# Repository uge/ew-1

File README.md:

# Pi 5 Corona HV supply

The canonical working design is **N-layout-17-hv-warnings**. Open
[pi5_corona_hv.kicad_pro](hardware/pi5_corona_hat_direct/pi5_corona_hv.kicad_pro)
in **KiCad 10**. This is the active editable project, including the accepted
component substitutions, completed routing and front/back high-voltage warnings.

- [Project guide](hardware/pi5_corona_hat_direct/README.md)
- [Current JLCPCB package](hardware/pi5_corona_hat_direct/exports/jlcpcb-N-layout-17-hv-warnings-package.zip)
- [Front preview](hardware/pi5_corona_hat_direct/renders/hv-warning-front.png) / [back preview](hardware/pi5_corona_hat_direct/renders/hv-warning-back.png)
- [Design status and unresolved issues](hardware/pi5_corona_hat_direct/AUDIT.md)
- [Export and validation commands](hardware/pi5_corona_hat_direct/layout/README.md)

Old project copies, trial boards, revision snapshots and stale generated outputs
have been removed from the working tree. Earlier tracked versions remain in Git
history. Historical design notes under `docs/` are reference material; the project
guide and native files above take precedence. The `doc` link is an alias of `docs`.

The working version is not a qualified 15 kV production release. Native ERC/DRC
checks do not replace the outstanding insulation, surge and component qualification.

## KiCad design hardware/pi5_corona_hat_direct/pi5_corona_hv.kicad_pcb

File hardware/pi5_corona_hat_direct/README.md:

# Working design — N-layout-17-hv-warnings

Open `pi5_corona_hv.kicad_pro` in KiCad 10. The adjacent PCB, root schematic,
five hierarchical sheets, custom symbol/footprint libraries and 3D assets form
the single working project. Standard KiCad 10 libraries must be installed separately.
Keep all these project files together; library tables use `${KIPRJMOD}` paths.

The board is two-layer, 1.6 mm thick, with a 196 × 120 mm carrier and five
break-off mini boards (231 × 120 mm overall envelope). Accepted LV routing,
the shortened HV return surge path and large warning graphics on both sides
are present in the native PCB. DNP parts are C63/R64; MP1 is a DNP mechanical reference.

| References | Current selection |
|---|---|
| C100–C111 | STE A12B1D102KN0B0S0N0 / C249245; 1 nF, 6 kV, Y5P, 10%, 10 mm pitch |
| R20–R29 | Bourns CHV2512-JW-106ELF / C2095568; 10 MΩ, 5%, 1 W, 3 kV, 2512 |
| D51 | hongjiacheng SMBJ22A / C49066946 |
| T1 | Coilcraft FL2015-4LD; external sourcing required |

Use the current JLCPCB deliverables for Gerbers/drills, BOM and CPL: 159 components
across 53 matching BOM rows. `exports/jlcpcb-bom.csv`, `exports/jlcpcb-cpl.csv` and
`exports/jlcpcb-gerbers.zip` are the upload files. Only T1 remains a purchased-component
external-source exception. DNP parts and PCB-only features are excluded.

[Front](renders/hv-warning-front.png) and [back](renders/hv-warning-back.png)
previews show current markings. These are diagnostic layer previews, not 3D assembly
fit certification. Dated procurement evidence remains under `procurement/`.
Stock evidence is a snapshot, not a reservation or guarantee of orderability.

[Pi 5 host runbook](host/RUNBOOK.md) prepares ew-1 for the board; [Pi Zero 2W mixed AP guide](host/ZERO2W_MIXED_AP.md) configures `ew-1-zero-2w.local` for concurrent Wi-Fi client + AP operation; [bring-up log](host/BRINGUP.md), [handoff summary](host/HANDOFF.md), and [HUSB238A notes](host/HUSB238A.md) record current bench state and USB-PD driver behavior.
[Validation/export instructions](layout/README.md) reproduce current outputs.
[Design status](AUDIT.md) records the unresolved HV and procurement issues.
The native files are the working design, not an archival or experimental copy.
Earlier tracked versions can be recovered from Git history.

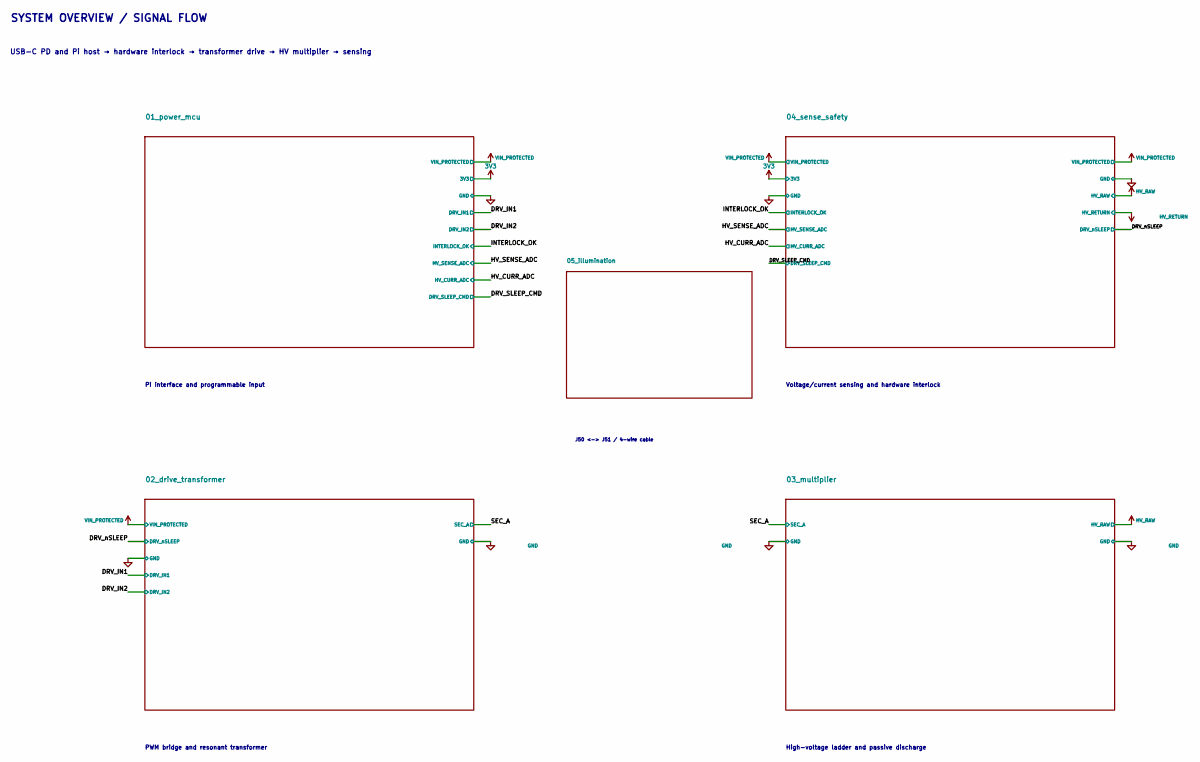
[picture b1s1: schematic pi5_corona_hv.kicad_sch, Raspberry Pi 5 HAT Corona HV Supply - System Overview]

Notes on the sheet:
SYSTEM OVERVIEW / SIGNAL FLOW
High-voltage ladder and passive discharge
Pi interface and programmable input
J50 <-> J51 / 4-wire cable
Voltage/current sensing and hardware interlock
USB-C PD and Pi host → hardware interlock → transformer drive → HV multiplier → sensing
PWM bridge and resonant transformer

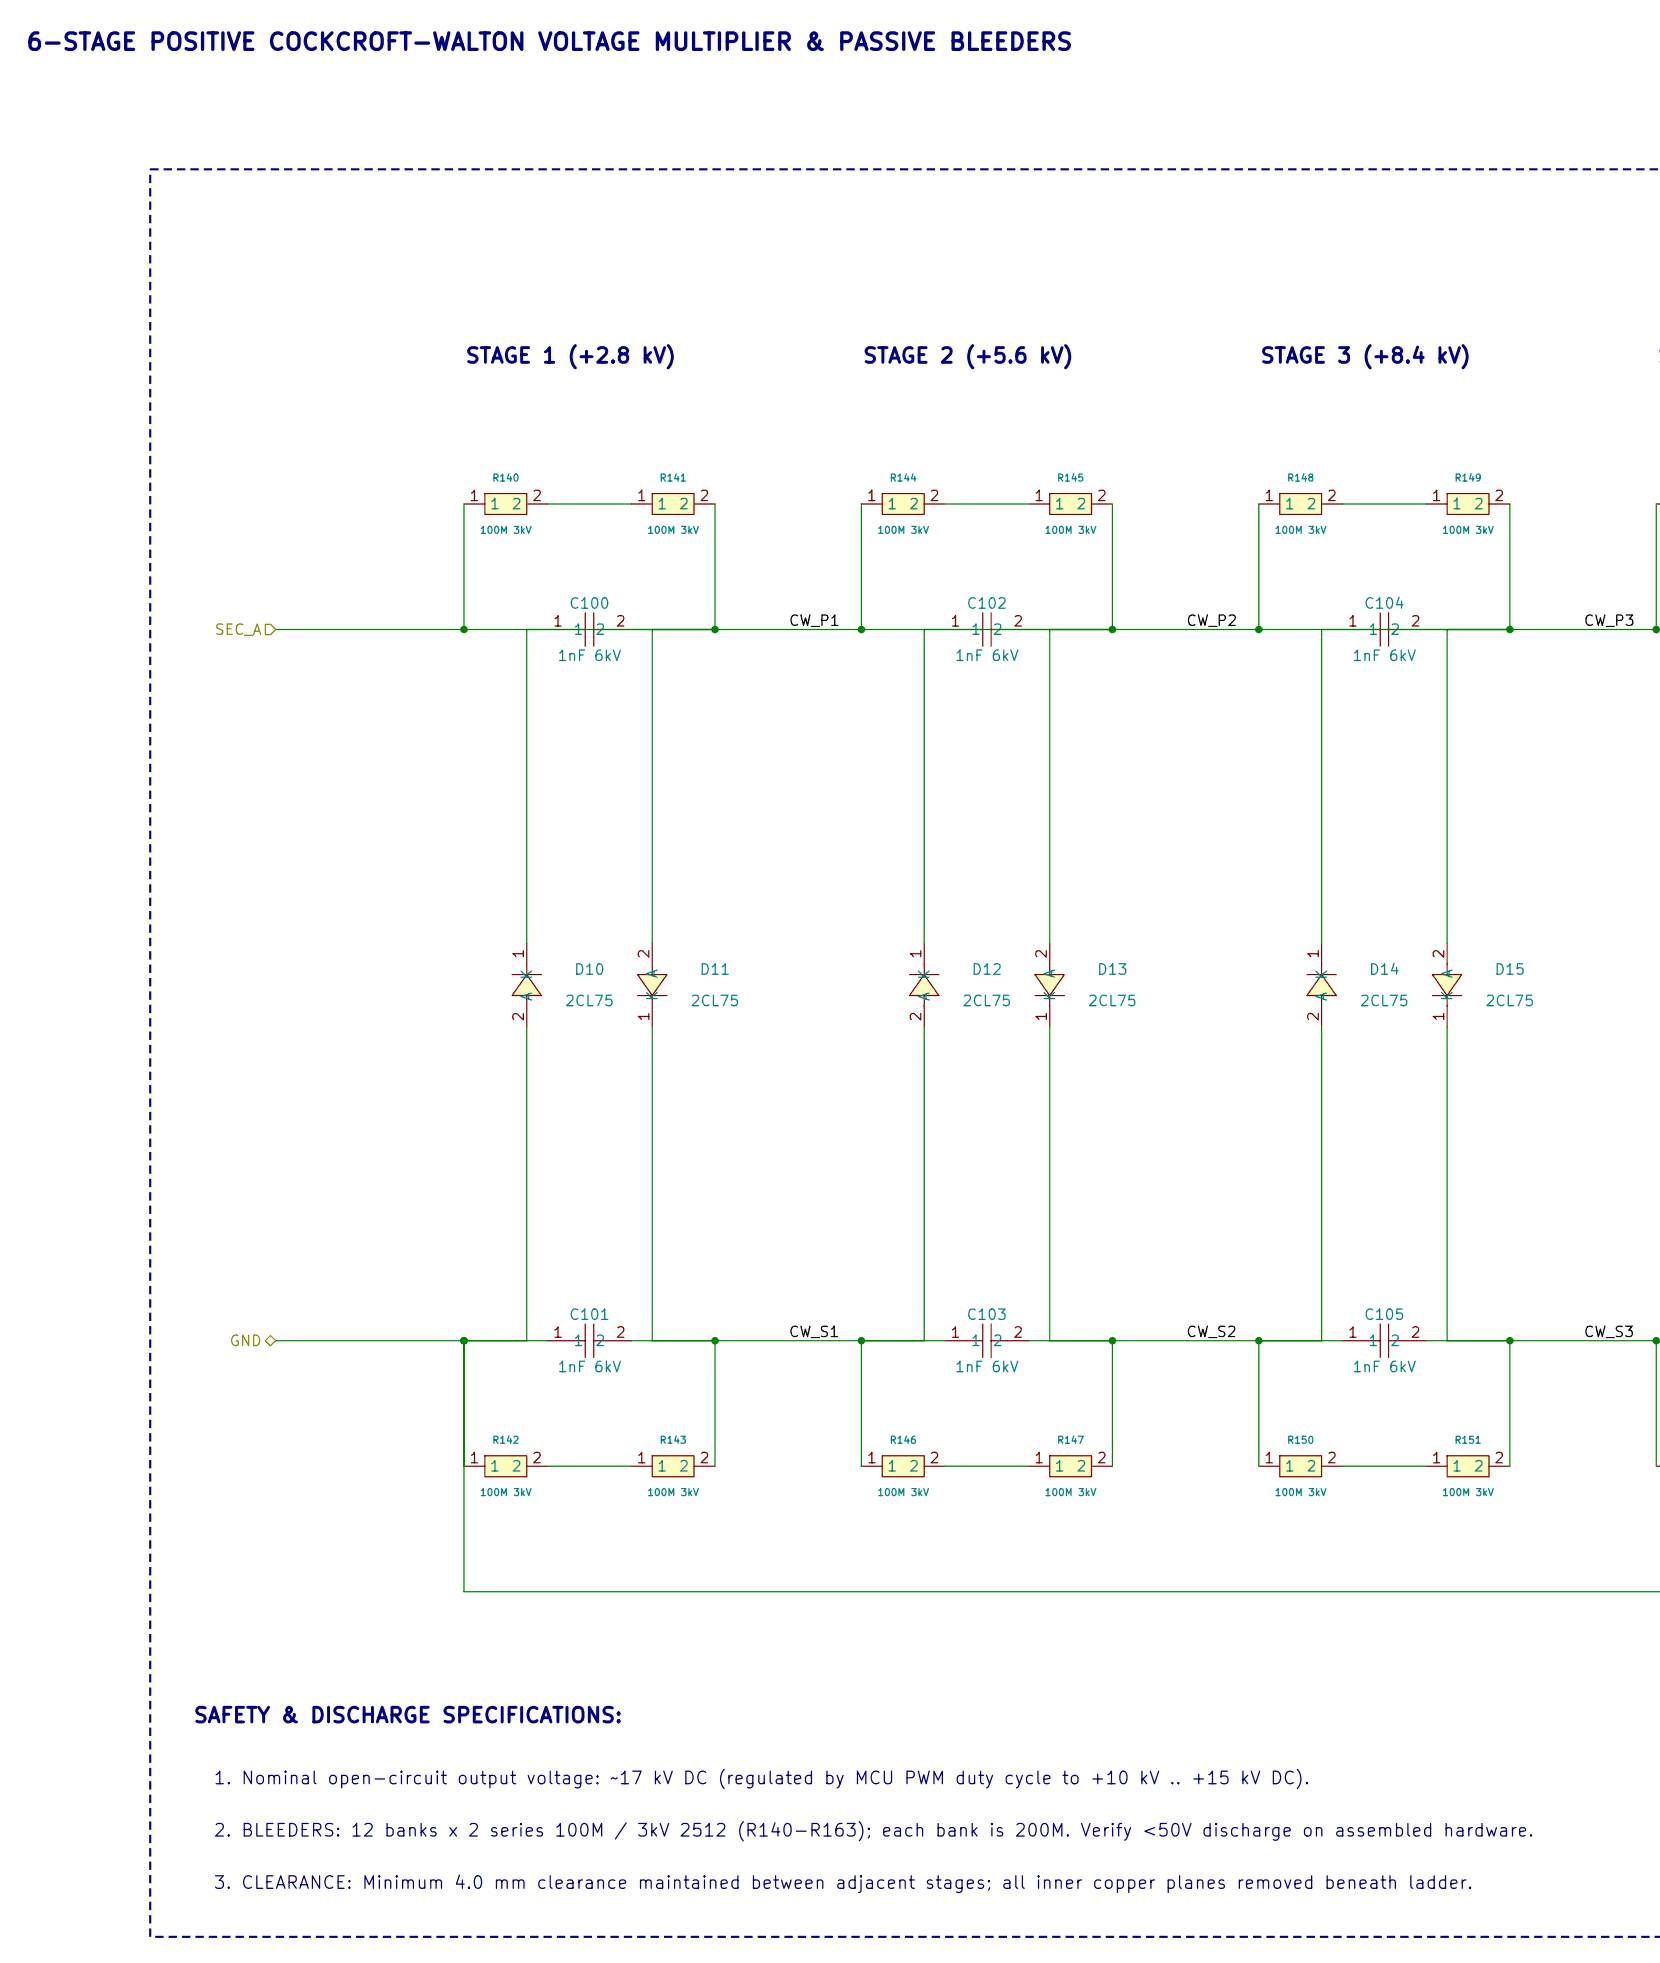
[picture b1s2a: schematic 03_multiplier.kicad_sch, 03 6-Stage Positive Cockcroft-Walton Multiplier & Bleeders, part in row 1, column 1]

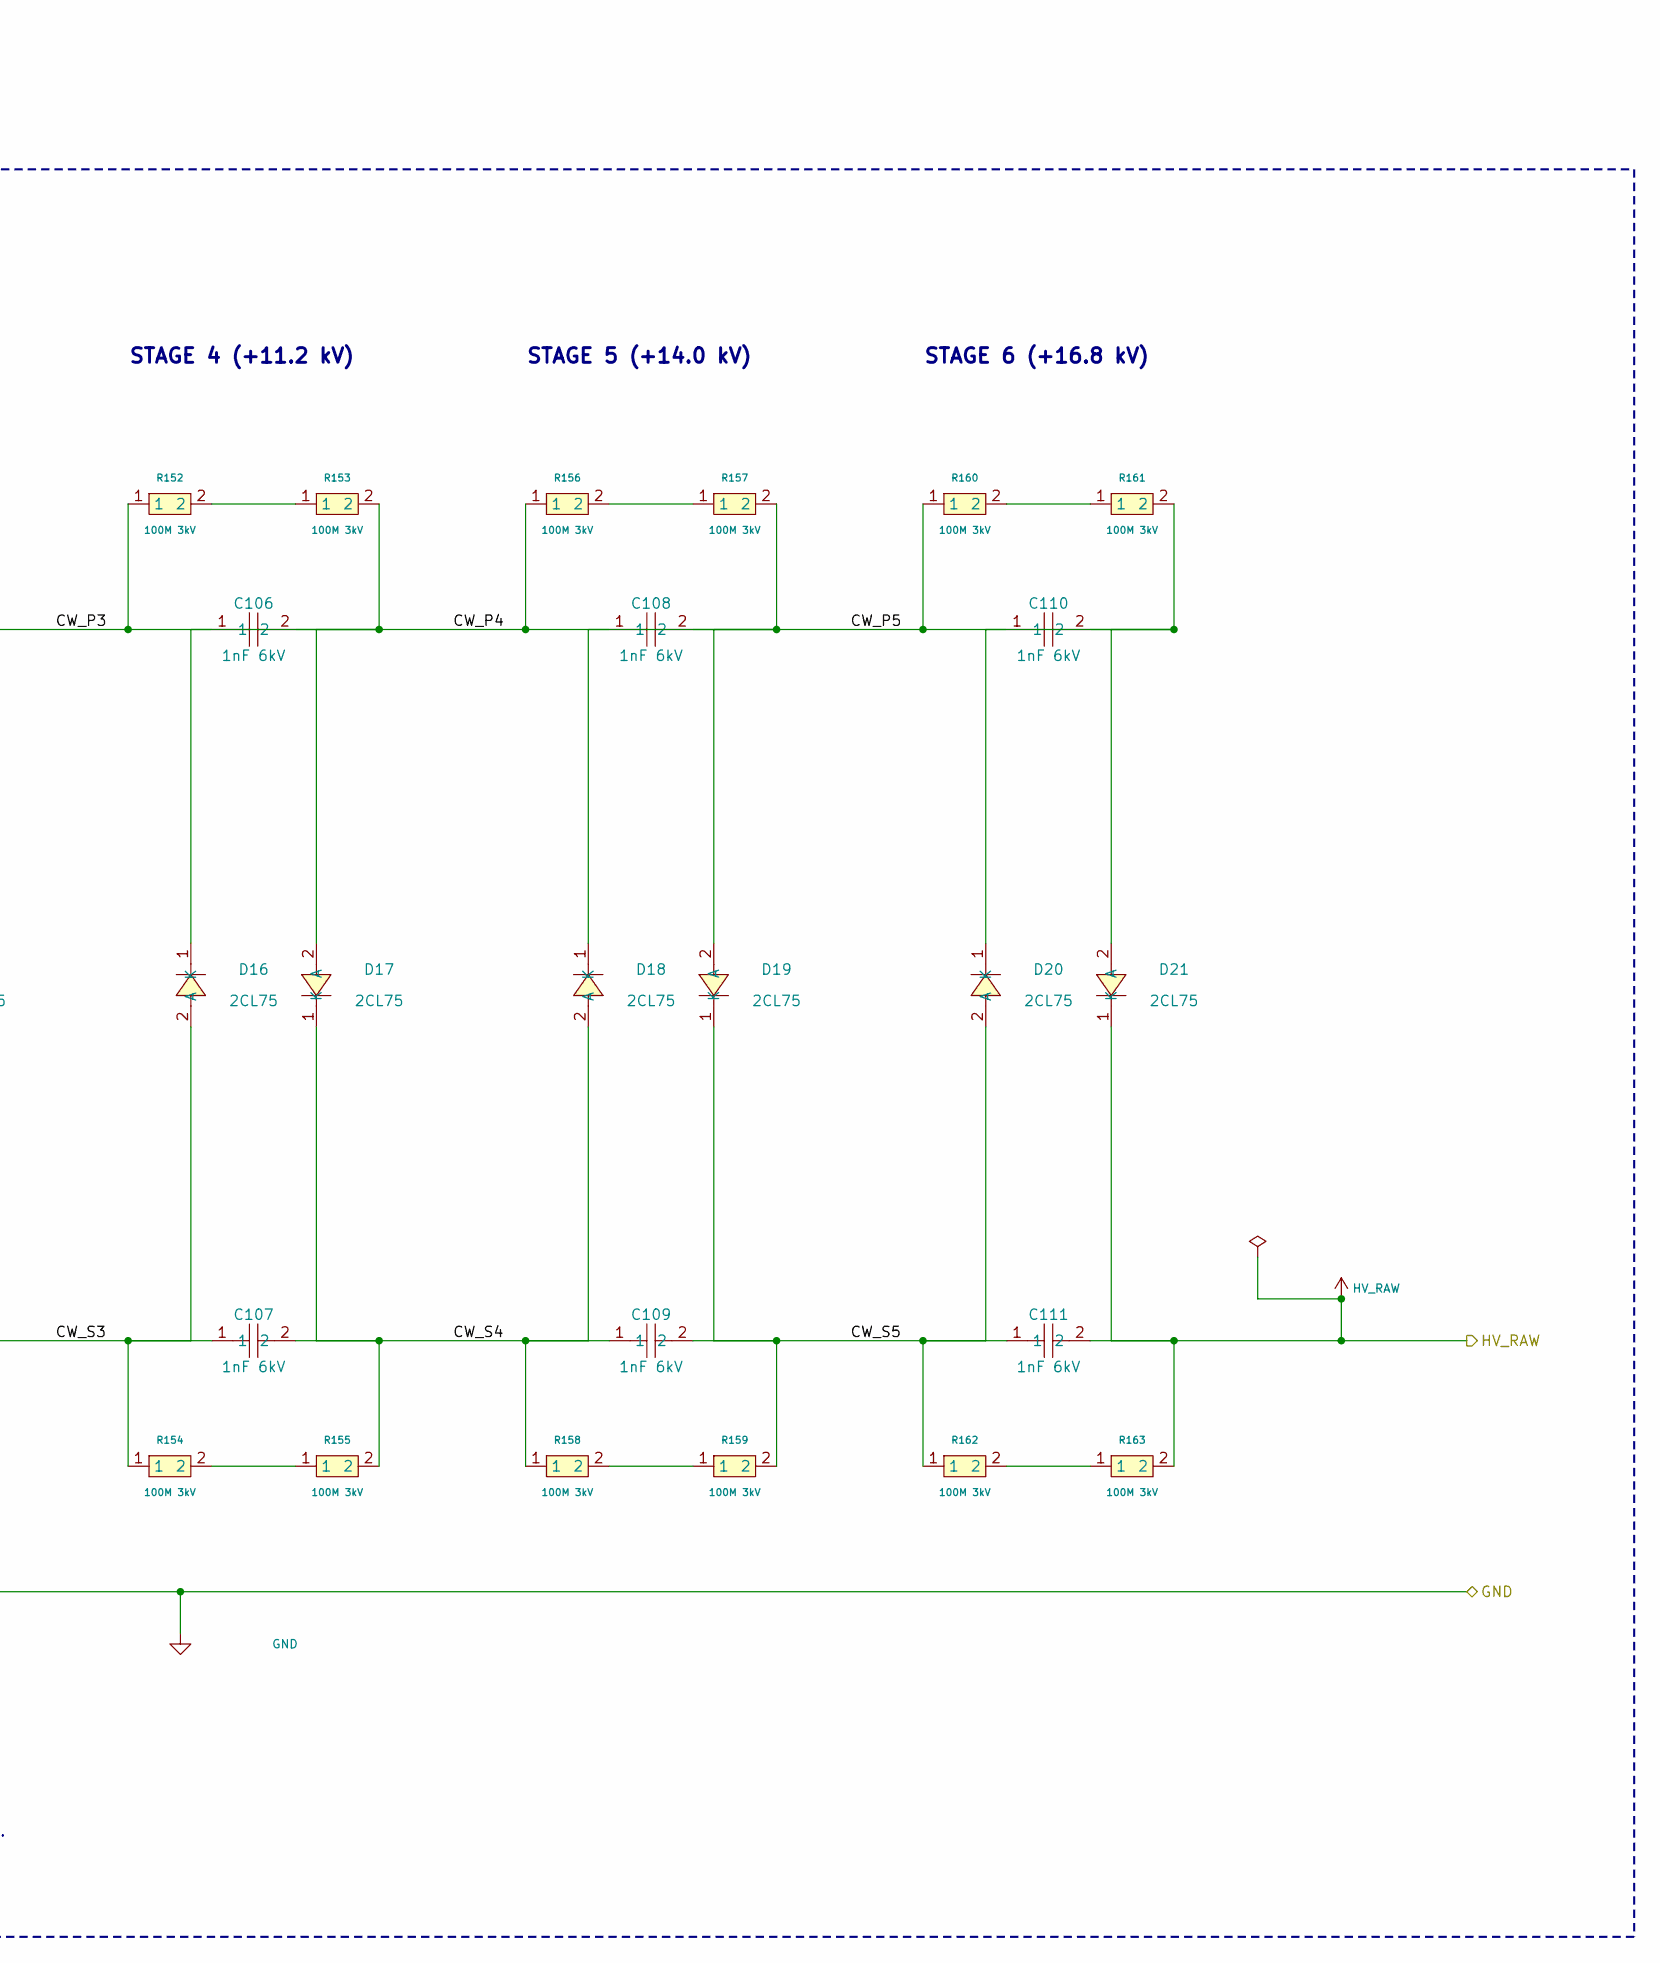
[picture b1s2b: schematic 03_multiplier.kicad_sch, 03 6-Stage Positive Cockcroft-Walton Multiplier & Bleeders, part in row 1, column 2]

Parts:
C100, C101, C102, C103, C104, C105, C106, C107, C108, C109, C110, C111: 1nF 6kV; STE_A12B1D102K_P10.0mm; MPN A12B1D102KN0B0S0N0; LCSC Part C249245
D10, D11, D12, D13, D14, D15, D16, D17, D18, D19, D20, D21: 2CL75; Sunmate_2CL75_D3_L12_P26; MPN 2CL75; LCSC Part C424512
R140, R141, R142, R143, R144, R145, R146, R147, R148, R149, R150, R151, R152, R153, R154, R155, R156, R157, R158, R159, R160, R161, R162, R163: 100M 3kV; R_2512_6332Metric; MPN CHV2512-JW-107ELF; LCSC Part C2089706

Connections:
/03_multiplier/CW_P1: C100.2, C102.1, D10.1 (K), D11.2 (A), R141.2, R144.1
/03_multiplier/CW_P2: C102.2, C104.1, D12.1 (K), D13.2 (A), R145.2, R148.1
/03_multiplier/CW_P3: C104.2, C106.1, D14.1 (K), D15.2 (A), R149.2, R152.1
/03_multiplier/CW_P4: C106.2, C108.1, D16.1 (K), D17.2 (A), R153.2, R156.1
/03_multiplier/CW_P5: C108.2, C110.1, D18.1 (K), D19.2 (A), R157.2, R160.1
/03_multiplier/CW_S1: C101.2, C103.1, D11.1 (K), D12.2 (A), R143.2, R146.1
/03_multiplier/CW_S2: C103.2, C105.1, D13.1 (K), D14.2 (A), R147.2, R150.1
/03_multiplier/CW_S3: C105.2, C107.1, D15.1 (K), D16.2 (A), R151.2, R154.1
/03_multiplier/CW_S4: C107.2, C109.1, D17.1 (K), D18.2 (A), R155.2, R158.1
/03_multiplier/CW_S5: C109.2, C111.1, D19.1 (K), D20.2 (A), R159.2, R162.1
/HV_RAW: C111.2, D21.1 (K), R163.2; also elsewhere on the board
/SEC_A: C100.1, R140.1; also elsewhere on the board
GND: C101.1, D10.2 (A), R142.1; also elsewhere on the board
unnamed: C110.2, D20.1 (K), D21.2 (A), R161.2
unnamed: R140.2, R141.1
unnamed: R142.2, R143.1
unnamed: R144.2, R145.1
unnamed: R146.2, R147.1
unnamed: R148.2, R149.1
unnamed: R150.2, R151.1
unnamed: R152.2, R153.1
unnamed: R154.2, R155.1
unnamed: R156.2, R157.1
unnamed: R158.2, R159.1
unnamed: R160.2, R161.1
unnamed: R162.2, R163.1

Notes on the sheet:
SAFETY & DISCHARGE SPECIFICATIONS:
STAGE 2 (+5.6 kV)
STAGE 3 (+8.4 kV)
STAGE 4 (+11.2 kV)
STAGE 6 (+16.8 kV)
2. BLEEDERS: 12 banks x 2 series 100M / 3kV 2512 (R140-R163); each bank is 200M. Verify <50V discharge on assembled hardware.
STAGE 1 (+2.8 kV)
3. CLEARANCE: Minimum 4.0 mm clearance maintained between adjacent stages; all inner copper planes removed beneath ladder.
6-STAGE POSITIVE COCKCROFT-WALTON VOLTAGE MULTIPLIER & PASSIVE BLEEDERS
1. Nominal open-circuit output voltage: ~17 kV DC (regulated by MCU PWM duty cycle to +10 kV .. +15 kV DC).
STAGE 5 (+14.0 kV)

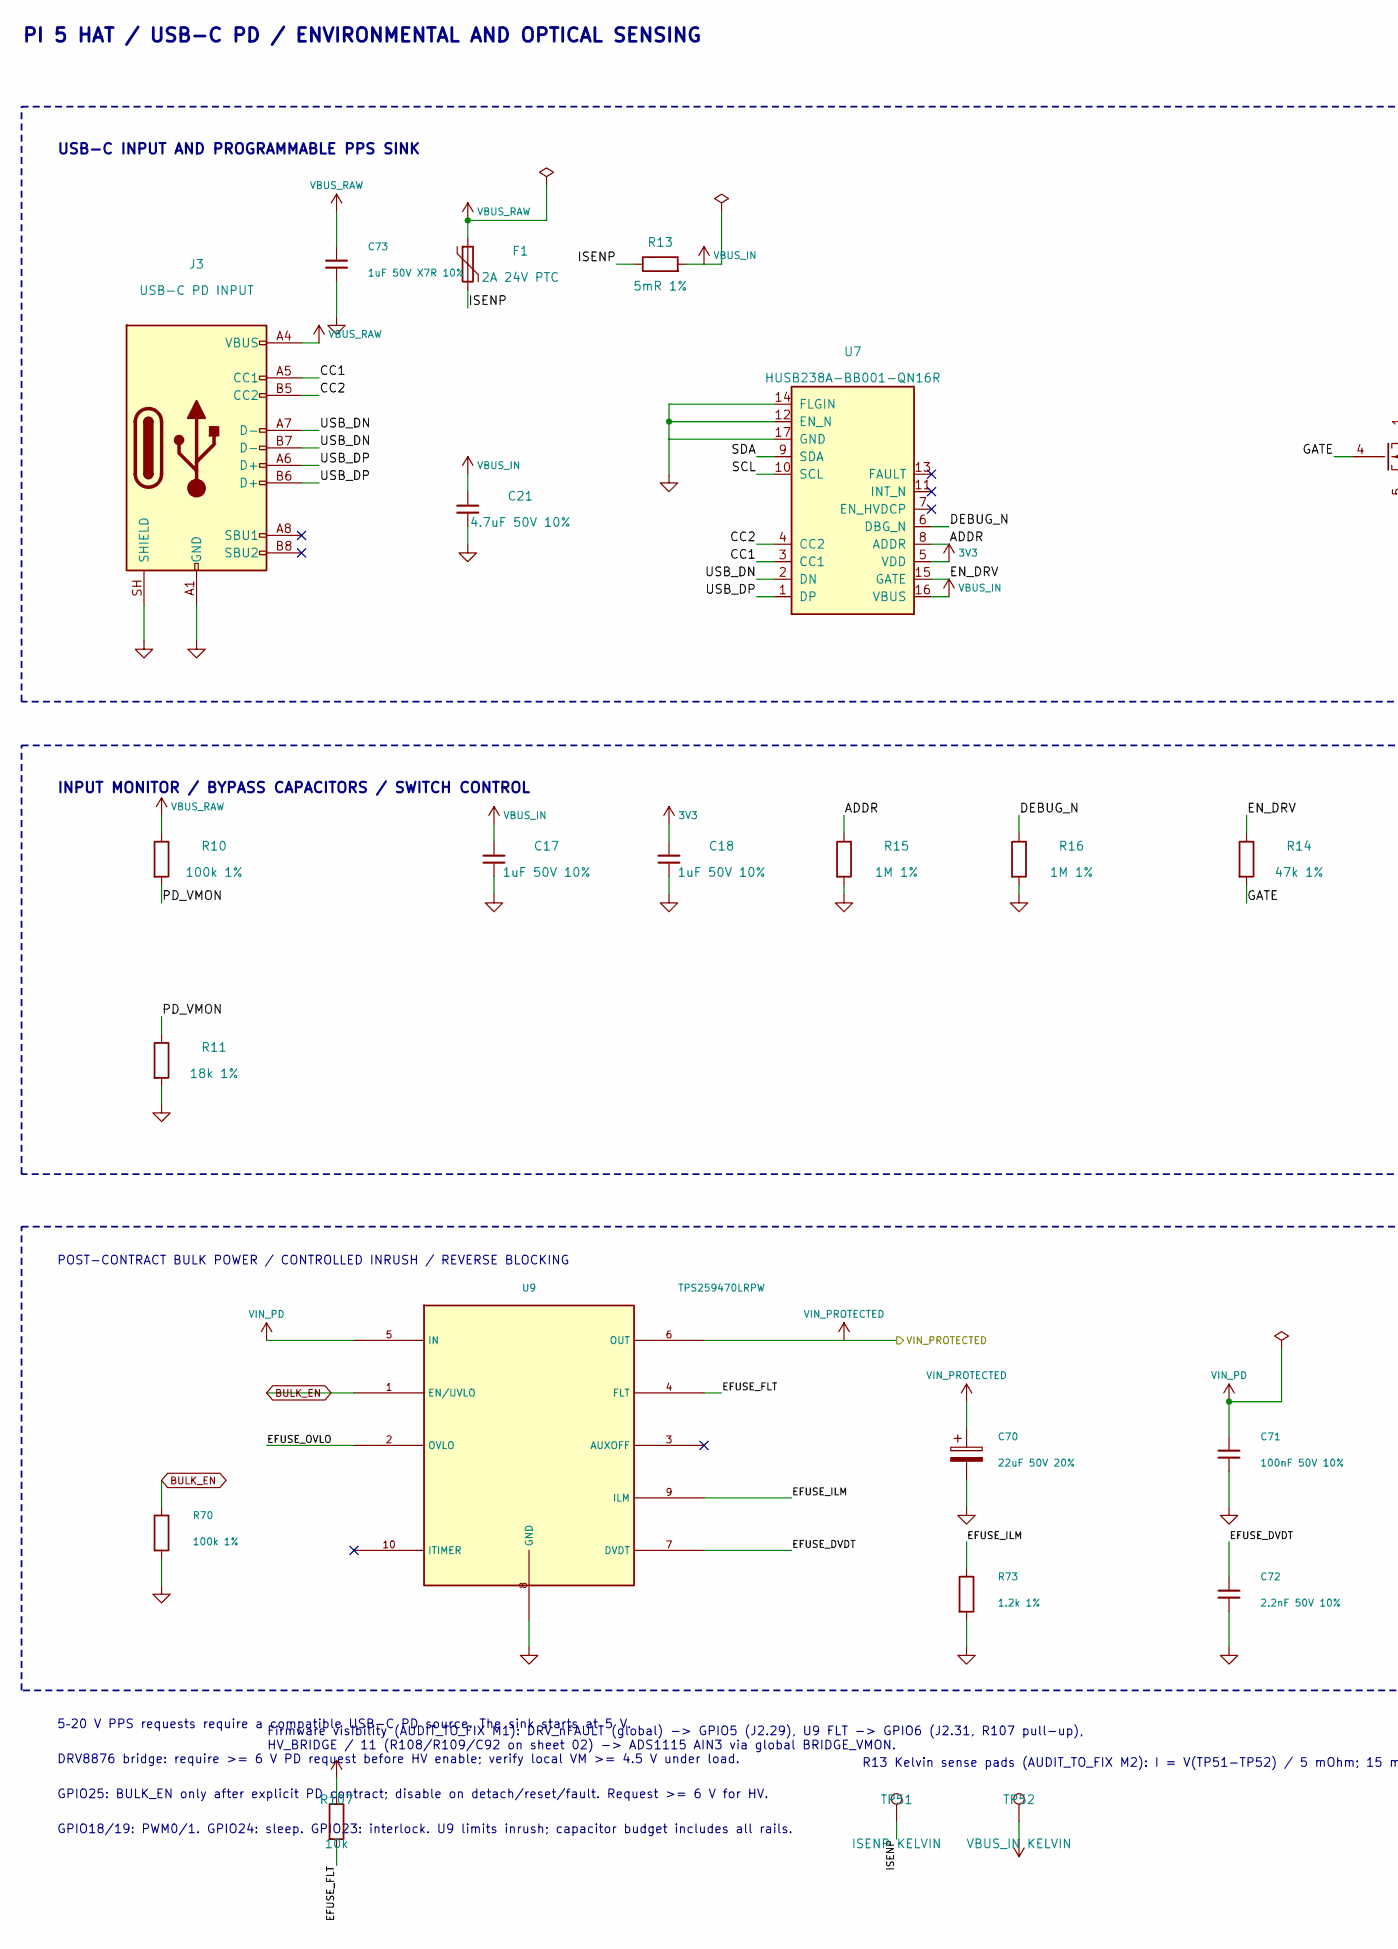
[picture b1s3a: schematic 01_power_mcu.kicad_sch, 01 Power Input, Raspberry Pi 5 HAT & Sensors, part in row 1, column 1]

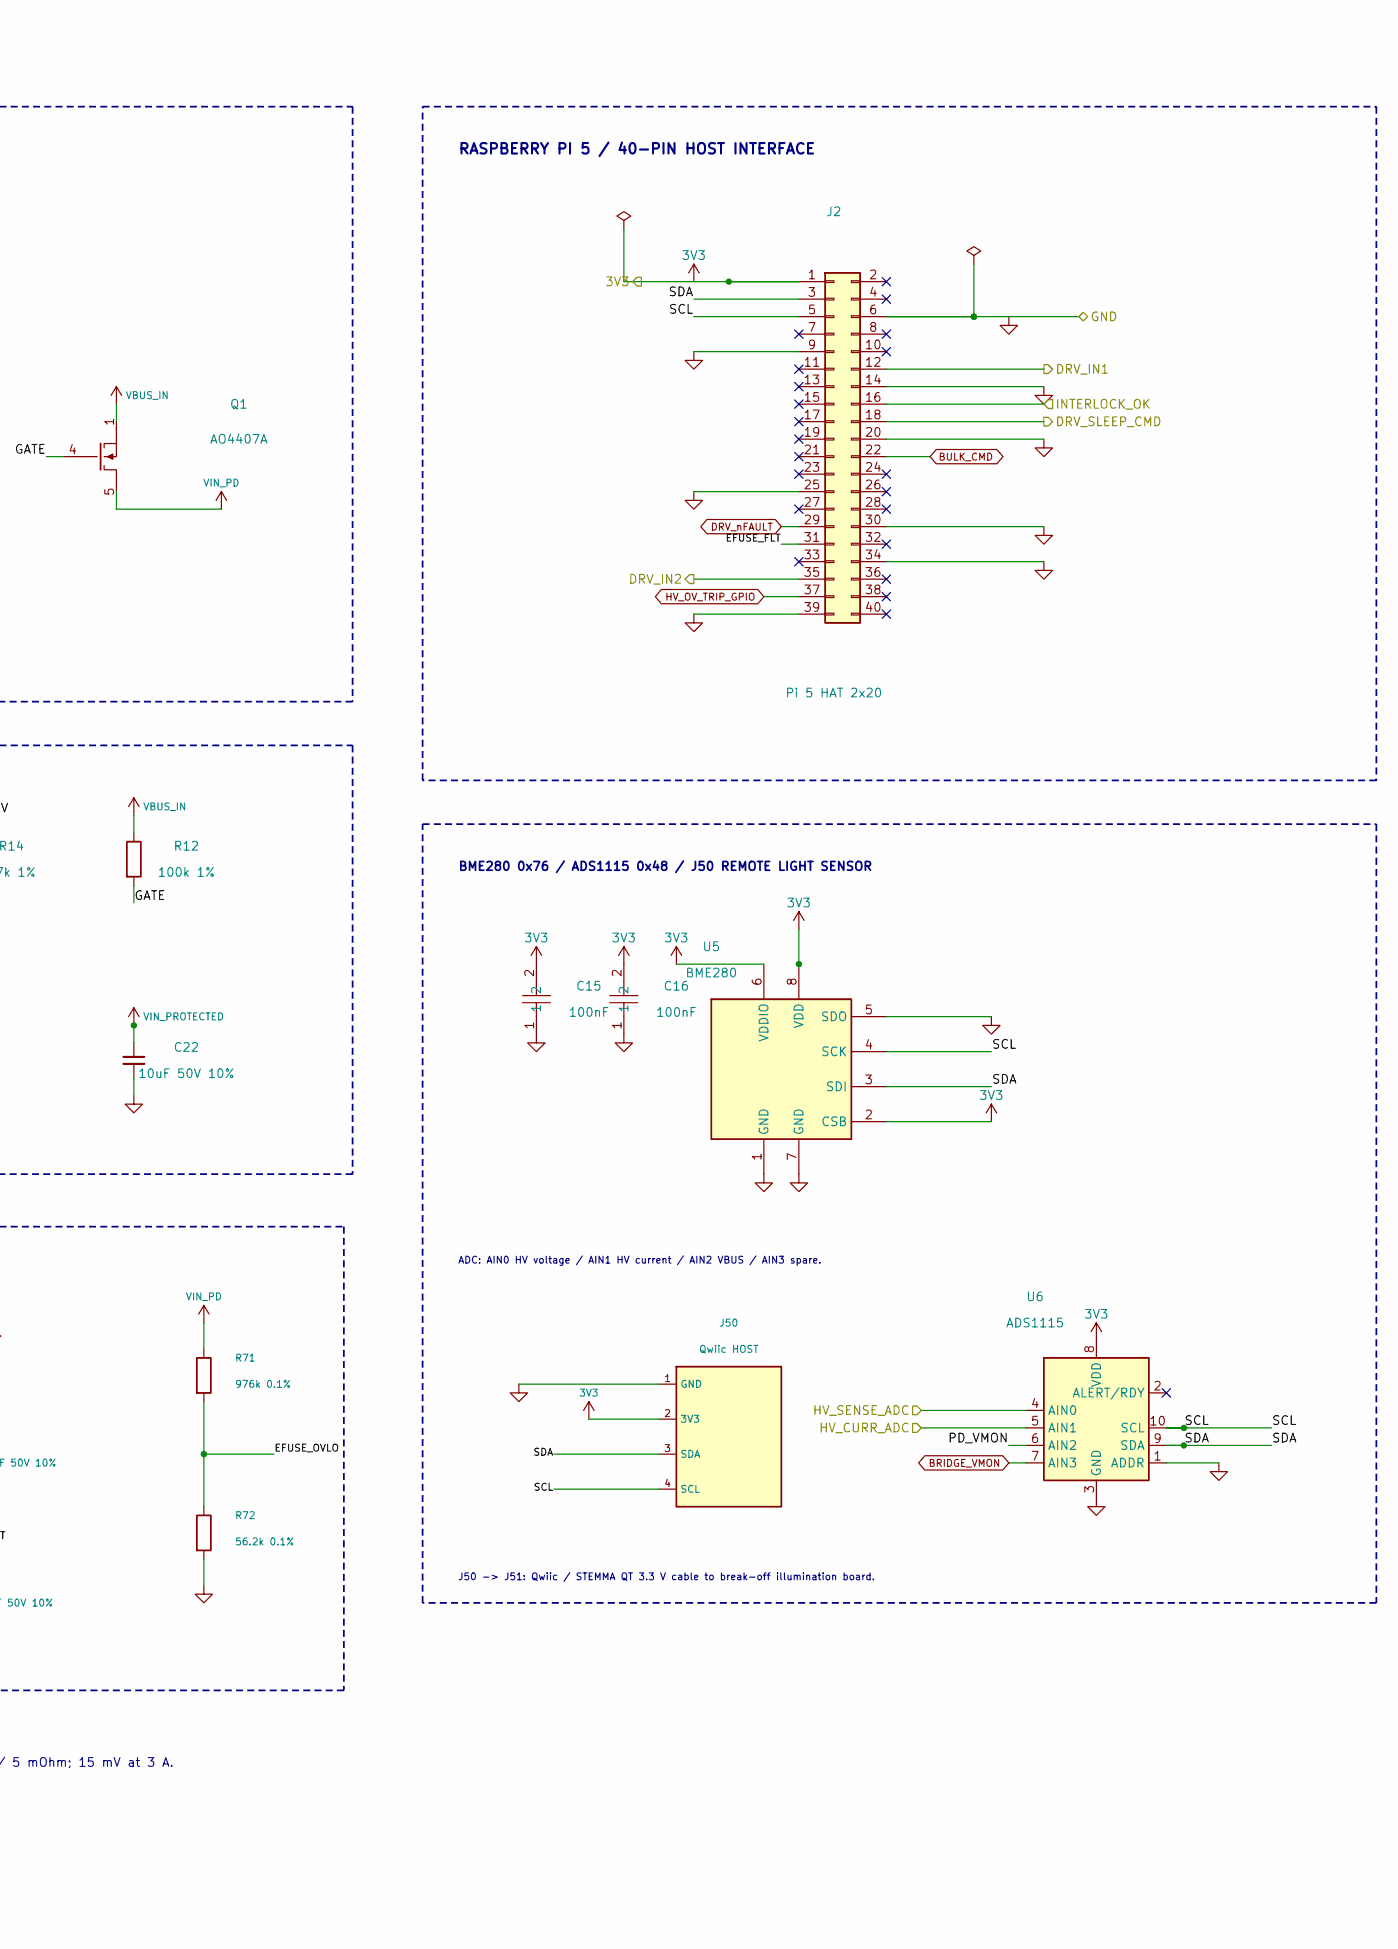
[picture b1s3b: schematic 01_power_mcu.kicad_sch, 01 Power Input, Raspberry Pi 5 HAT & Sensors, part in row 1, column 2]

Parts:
C15, C16: 100nF; C0603; MPN CC0603KRX7R9BB104; LCSC C14663
C17: 1uF 50V 10%; C_0603_1608Metric; MPN CL10B105KB8NQNC; LCSC C5199872
C18: 1uF 50V 10%; C_0603_1608Metric; MPN CL10A105KB8NNNC; LCSC C15849
C21: 4.7uF 50V 10%; C_1210_3225Metric; MPN GCM32ER71H475KA55L; LCSC C126618
C22: 10uF 50V 10%; C_1210_3225Metric; MPN UMK325AB7106KMHP; LCSC C386166
C70: 22uF 50V 20%; CP_Radial_D5.0mm_P2.00mm; MPN 50YXF22MEFC5X11; LCSC C88755
C71: 100nF 50V 10%; C_0603_1608Metric; MPN CC0603KRX7R9BB104; LCSC C14663
C72: 2.2nF 50V 10%; C_0603_1608Metric; MPN 0603B222K500NT; LCSC C1604
C73: 1uF 50V X7R 10%; C_0603_1608Metric; MPN CL10B105KB8NQNC; LCSC C5199872
F1: 2A 24V PTC; Fuse_1206_3216Metric; MPN 1206L200/24NR; LCSC C42396578
J2: Pi 5 HAT 2x20; PinSocket_2x20_P2.54mm_Vertical; MPN 2.54-2*20; LCSC C2977589
J3: USB-C PD INPUT; USB_C_Receptacle_HRO_TYPE-C-31-M-12; MPN TYPE-C-31-M-12; LCSC C165948
J50: Qwiic HOST; JST_SH_SM04B-SRSS-TB_1x04-1MP_P1.00mm_Horizontal; MPN SM04B-SRSS-TB(LF)(SN); LCSC C160404
Q1: AO4407A; SO-8_3.9x4.9mm_P1.27mm; MPN AO4407A; LCSC C16072
R10, R12, R70: 100k 1%; R_0603_1608Metric; MPN 0603WAF1003T5E; LCSC C25803
R11: 18k 1%; R_0603_1608Metric; MPN 0603WAF1802T5E; LCSC C25810
R13: 5mR 1%; R_2512_6332Metric; MPN RLP25FEGMR005; LCSC C393074
R14: 47k 1%; R_0603_1608Metric; MPN 0603WAF4702T5E; LCSC C25819
R15, R16: 1M 1%; R_0603_1608Metric; MPN 0603WAF1004T5E; LCSC C22935
R71: 976k 0.1%; R_0805_2012Metric; MPN RT0805BRD07976KL; LCSC C865713
R72: 56.2k 0.1%; R_0603_1608Metric; MPN RT0603BRD0756K2L; LCSC C705784
R73: 1.2k 1%; R_0603_1608Metric; MPN 0603WAF1201T5E; LCSC C22765
R107: 10k; R_0603_1608Metric; MPN 0603WAF1002T5E; LCSC Part C25804
TP51: ISENP KELVIN; TestPoint_Pad_D1.0mm
TP52: VBUS_IN KELVIN; TestPoint_Pad_D1.0mm
U5: BME280; Bosch_LGA-8_2.5x2.5mm_P0.65mm_ClockwisePinNumbering; MPN BME280; LCSC C92489
U6: ADS1115; TSSOP-10_3x3mm_P0.5mm; MPN ADS1115IDGSR; LCSC C37593
U7: HUSB238A-BB001-QN16R; QFN-16-1EP_3x3mm_P0.5mm_EP1.7x1.7mm; MPN HUSB238A-BB001-QN16R; LCSC C24833806
U9: TPS259470LRPW; Texas_RPW0010A_VQFN-HR-10_2x2mm; MPN TPS259470LRPWR; LCSC C3662793

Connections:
3V3: C15.2, C16.2, C18.1, J2.1, J50.2 (3V3), R107.1, U5.2 (CSB), U5.6 (VDDIO), U5.8 (VDD), U6.8 (VDD), U7.5 (VDD); also elsewhere on the board
/01_power_mcu/ADDR: R15.1, U7.8 (ADDR)
/01_power_mcu/CC1: J3.A5 (CC1), U7.3 (CC1)
/01_power_mcu/CC2: J3.B5 (CC2), U7.4 (CC2)
/01_power_mcu/DEBUG_N: R16.1, U7.6 (DBG_N)
/01_power_mcu/EFUSE_DVDT: C72.1, U9.7 (DVDT)
/01_power_mcu/EFUSE_FLT: J2.31, R107.2, U9.4 (FLT)
/01_power_mcu/EFUSE_ILM: R73.1, U9.9 (ILM)
/01_power_mcu/EFUSE_OVLO: R71.2, R72.1, U9.2 (OVLO)
/01_power_mcu/EN_DRV: R14.1, U7.15 (GATE)
/01_power_mcu/GATE: Q1.4 (G), R12.2, R14.2
/01_power_mcu/ISENP: F1.2, R13.1, TP51.1
/01_power_mcu/PD_VMON: R10.2, R11.1, U6.6 (AIN2)
/01_power_mcu/SCL: J2.5, J50.4 (SCL), U5.4 (SCK), U6.10 (SCL), U7.10 (SCL)
/01_power_mcu/SDA: J2.3, J50.3 (SDA), U5.3 (SDI), U6.9 (SDA), U7.9 (SDA)
/01_power_mcu/USB_DN: J3.A7 (D-), J3.B7 (D-), U7.2 (DN)
/01_power_mcu/USB_DP: J3.A6 (D+), J3.B6 (D+), U7.1 (DP)
/01_power_mcu/VBUS_IN: C17.1, C21.1, Q1.1 (S), Q1.2 (S), Q1.3 (S), R12.1, R13.2, TP52.1, U7.16 (VBUS)
/01_power_mcu/VBUS_RAW: C73.1, F1.1, J3.A4 (VBUS), J3.A9 (VBUS), J3.B4 (VBUS), J3.B9 (VBUS), R10.1
/01_power_mcu/VIN_PD: C71.1, Q1.5 (D), Q1.6 (D), Q1.7 (D), Q1.8 (D), R71.1, U9.5 (IN)
/DRV_IN1: J2.12; also elsewhere on the board
/DRV_IN2: J2.35; also elsewhere on the board
/DRV_SLEEP_CMD: J2.18; also elsewhere on the board
/HV_CURR_ADC: U6.5 (AIN1); also elsewhere on the board
/HV_SENSE_ADC: U6.4 (AIN0); also elsewhere on the board
/INTERLOCK_OK: J2.16; also elsewhere on the board
/VIN_PROTECTED: C22.1, C70.1, U9.6 (OUT); also elsewhere on the board
BRIDGE_VMON: U6.7 (AIN3); also elsewhere on the board
BULK_CMD: J2.22; also elsewhere on the board
BULK_EN: R70.1, U9.1 (EN/UVLO); also elsewhere on the board
DRV_nFAULT: J2.29; also elsewhere on the board
GND: C15.1, C16.1, C17.2, C18.2, C21.2, C22.2, C70.2, C71.2, C72.2, C73.2, J2.6, J2.9, J2.14, J2.20, J2.25, J2.30, J2.34, J2.39, J3.A1 (GND), J3.A12 (GND), J3.B1 (GND), J3.B12 (GND), J3.SH (SHIELD), J50.1 (GND), R11.2, R15.2, R16.2, R70.2, R72.2, R73.2, U5.1 (GND), U5.5 (SDO), U5.7 (GND), U6.1 (ADDR), U6.3 (GND), U7.12 (EN_N), U7.14 (FLGIN), U7.17 (GND), U9.8 (GND); also elsewhere on the board
HV_OV_TRIP_GPIO: J2.37; also elsewhere on the board

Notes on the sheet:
DRV8876 bridge: require >= 6 V PD request before HV enable; verify local VM >= 4.5 V under load.
USB-C INPUT AND PROGRAMMABLE PPS SINK
RASPBERRY PI 5 / 40-PIN HOST INTERFACE
POST-CONTRACT BULK POWER / CONTROLLED INRUSH / REVERSE BLOCKING
GPIO18/19: PWM0/1. GPIO24: sleep. GPIO23: interlock. U9 limits inrush; capacitor budget includes all rails.
5–20 V PPS requests require a compatible USB-C PD source. The sink starts at 5 V.
PI 5 HAT / USB-C PD / ENVIRONMENTAL AND OPTICAL SENSING
ADC: AIN0 HV voltage / AIN1 HV current / AIN2 VBUS / AIN3 spare.
INPUT MONITOR / BYPASS CAPACITORS / SWITCH CONTROL
GPIO25: BULK_EN only after explicit PD contract; disable on detach/reset/fault. Request >= 6 V for HV.
BME280 0x76 / ADS1115 0x48 / J50 REMOTE LIGHT SENSOR
J50 -> J51: Qwiic / STEMMA QT 3.3 V cable to break-off illumination board.
Firmware visibility (AUDIT_TO_FIX M1): DRV_nFAULT (global) -> GPIO5 (J2.29), U9 FLT -> GPIO6 (J2.31, R107 pull-up), HV_BRIDGE / 11 (R108/R109/C92 on sheet 02) -> ADS1115 AIN3 via global BRIDGE_VMON.
R13 Kelvin sense pads (AUDIT_TO_FIX M2): I = V(TP51-TP52) / 5 mOhm; 15 mV at 3 A.
